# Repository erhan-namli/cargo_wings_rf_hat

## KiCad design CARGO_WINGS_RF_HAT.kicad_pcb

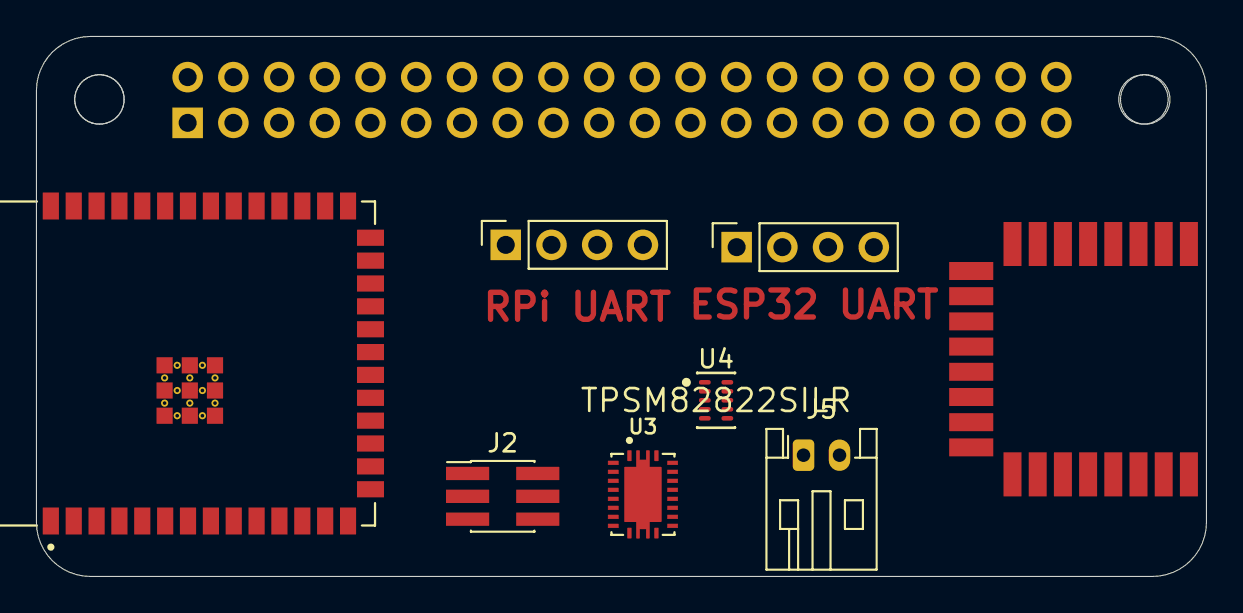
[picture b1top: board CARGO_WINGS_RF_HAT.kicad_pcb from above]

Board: 2 copper layers, 65.0 x 30.0 mm, 9 parts (1 on the bottom side), 5 nets, no tracks yet.

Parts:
J1: RPi_GPIO; PinSocket_2x20_P2.54mm_Vertical
J2: ESP Prog; PinHeader_2x03_P1.27mm_Vertical_SMD
J3, J4: Conn_01x04_Socket; PinSocket_1x04_P2.54mm_Vertical
J5: S2B-PH-K-S(LF)(SN); JST_PH_S2B-PH-K_1x02_P2.00mm_Horizontal
U1: DWM1000; XCVR_DWM1000
U2: ESP32-S3-WROOM-1-N8R2; XCVR_ESP32-S3-WROOM-1-N8R2
U3: TPS61088RHLT; IC_MSP430FR2522IRHLR
U4: TPSM82822SILR; Texas_Instruments-SIL0010D-0-0-MFG

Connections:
+3V3: U1.5 (VDDAON), U1.6 (VDD3V3@1), U1.7 (VDD3V3@2)
+BATT: J5.1, U3.9 (VIN), U4.1 (VIN), U4.2 (VIN), U4.3 (EN)
unnamed: U2.1 (GND), U2.40 (GND), U2.41_1 (GND), U2.41_2 (GND), U2.41_3 (GND), U2.41_4 (GND), U2.41_5 (GND), U2.41_6 (GND), U2.41_7 (GND), U2.41_8 (GND), U2.41_9 (GND)
unnamed: U3.4 (SW), U3.5 (SW), U3.6 (SW), U3.7 (SW)
unnamed: U3.14 (VOUT), U3.15 (VOUT), U3.16 (VOUT)

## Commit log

2023-12-31 Init
2024-01-01 Update
    - smps added
    - booster added 3.7V to 5V
2024-02-06 update
    - power circuit added
